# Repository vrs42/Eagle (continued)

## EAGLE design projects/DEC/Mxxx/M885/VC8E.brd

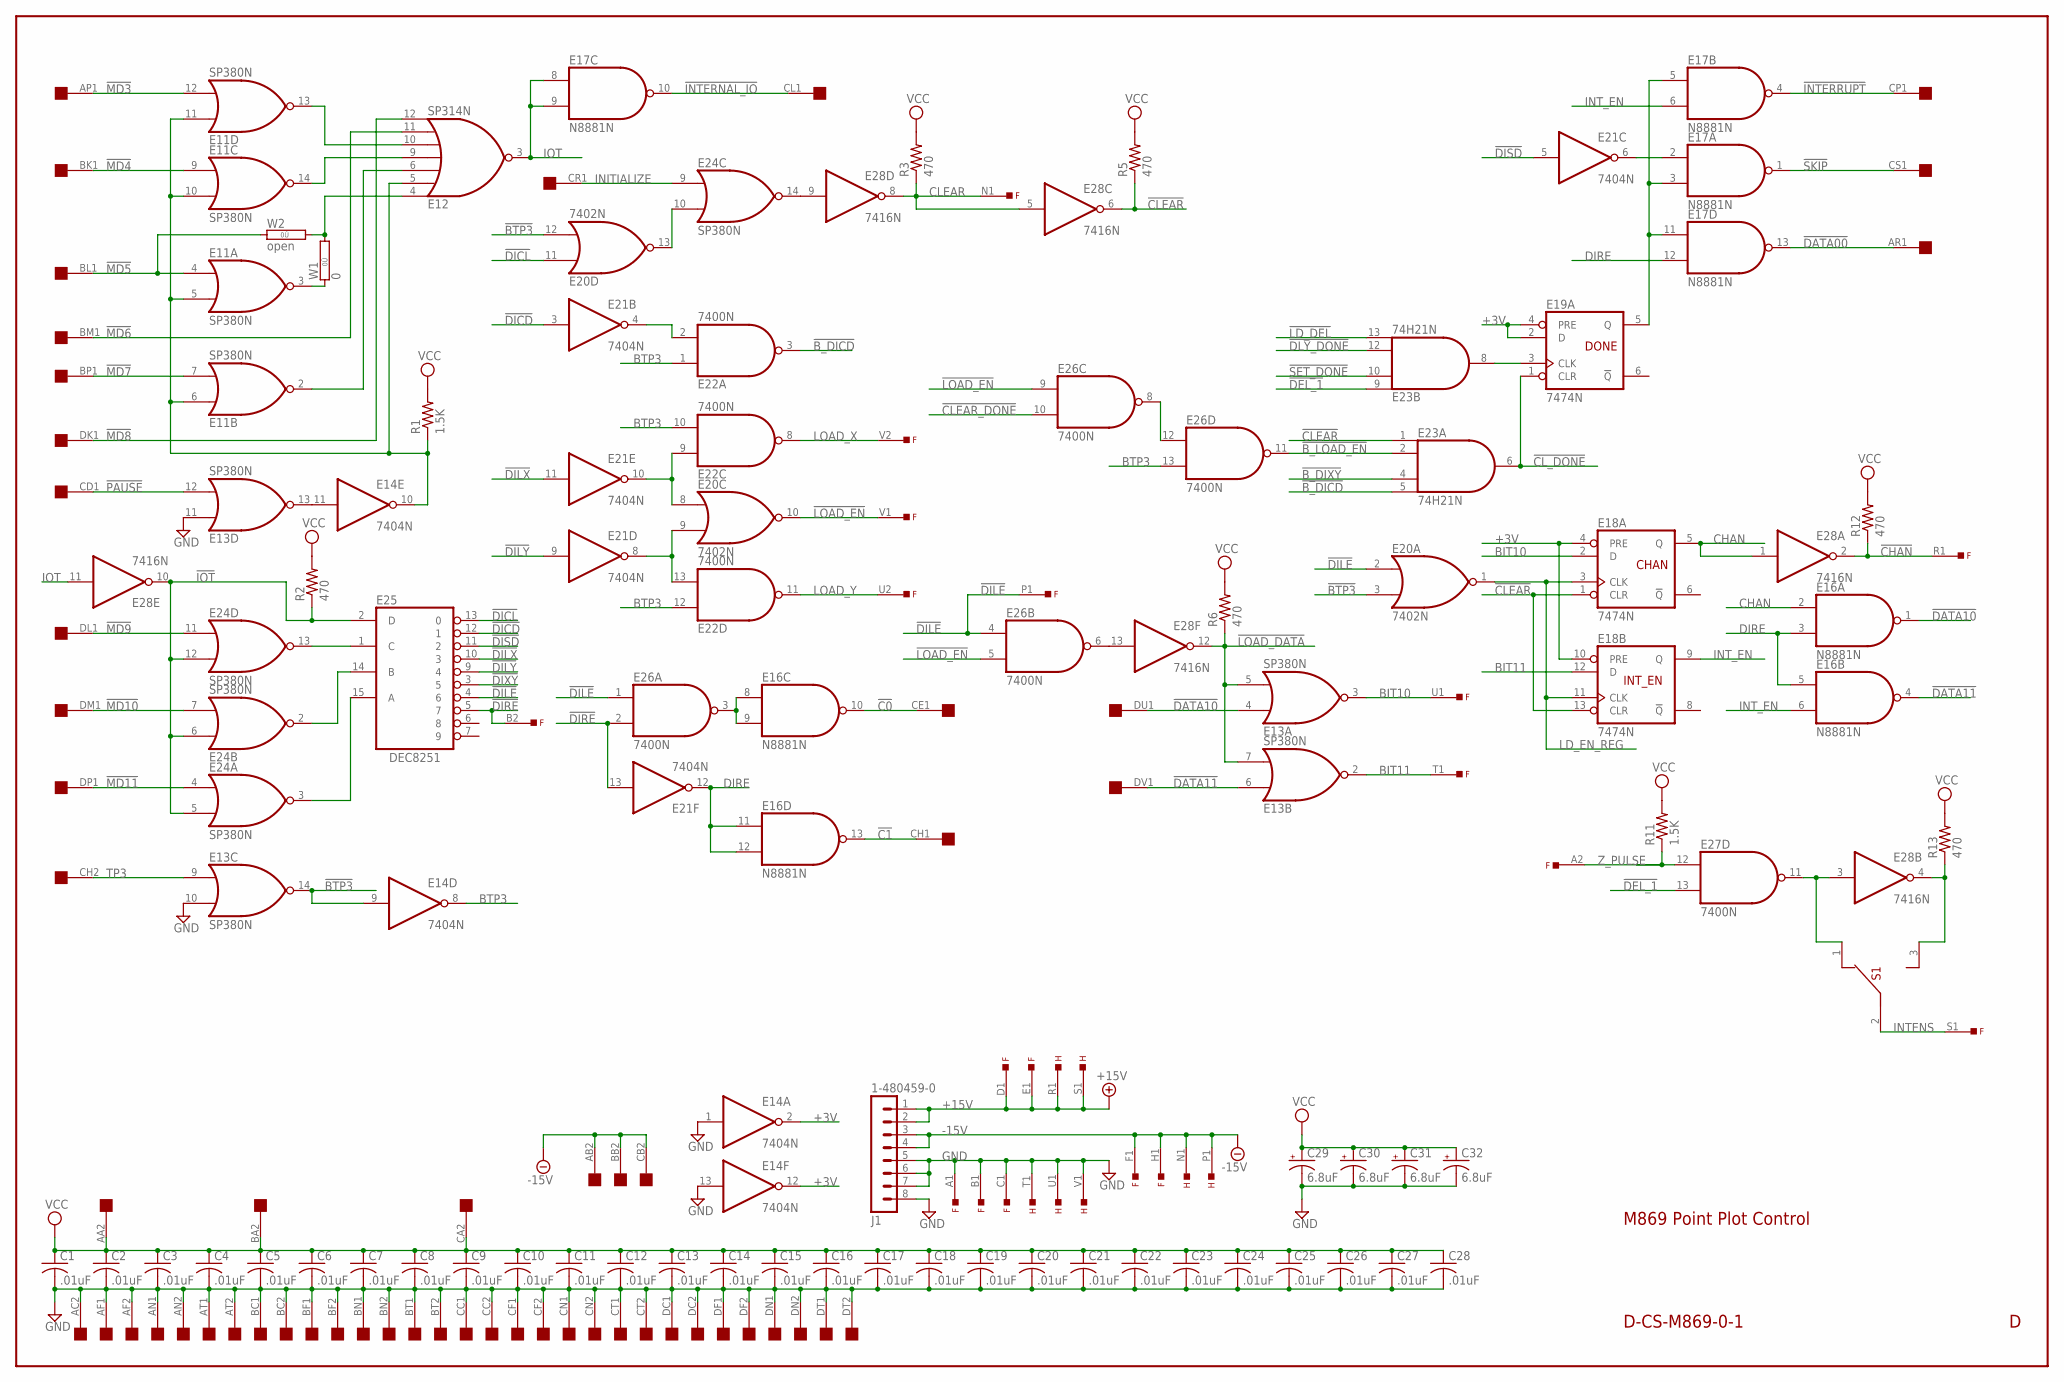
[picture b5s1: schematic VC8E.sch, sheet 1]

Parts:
C1, C2, C3, C4, C5, C6, C7, C8, C9, C10, C11, C12, C13, C14, C15, C16, C17, C18, C19, C20, C21, C22, C23, C24, C25, C26, C27, C28: .01uF; C063-025X075
C29, C30, C31, C32: 6.8uF; E12-8
E11, E13, E24: SP380N; DIL14
E12: SP314N; DIL14
E14, E21: 7404N; DIL14
E16, E17: N8881N; DIL14
E18, E19: 7474N; DIL14
E20: 7402N; DIL14
E22, E26, E27: 7400N; DIL14
E23: 74H21N; DIL14
E25: DEC8251; DIL16
E28: 7416N; DIL14
F: EDGE-TOP; EDGE-CON2
H: EDGE-TOP; EDGE-CON2
J1: 1-480459-0
OMNIBUS: QUAD; EDGE-CON8
R1, R11: 1.5K; 0207/10
R2, R3, R5, R6, R12, R13: 470; 0207/10
S1: 12-09698; 23-021
W1: 0; 0R/10
W2: open; 0R/10

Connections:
!BTP3: E13.14 (O), E14.9 (I), E20.3 (I1), E20.12 (I1)
!B_DICD: E22.3 (O), E23.5 (I3)
!B_DIXY: E23.4 (I2); also elsewhere on the board
!B_LOAD_EN: E23.2 (I1), E26.11 (O)
!C0: E16.10 (O), OMNIBUS.CE1
!C1: E16.13 (O), OMNIBUS.CH1
!CHAN: E28.2 (O), F.R1, R12.1; also elsewhere on the board
!CLEAR: E18.1 (CLR), E18.13 (CLR), E23.1 (I0), E28.6 (O), R5.1; also elsewhere on the board
!CLEAR_DONE: E26.10 (I1); also elsewhere on the board
!CL_DONE: E19.1 (CLR), E23.6 (O)
!DATA00: E17.13 (O), OMNIBUS.AR1
!DATA10: E13.4 (I0), E16.1 (O), OMNIBUS.DU1; also elsewhere on the board
!DATA11: E13.6 (I0), E16.4 (O), OMNIBUS.DV1; also elsewhere on the board
!DEL_1: E23.9 (I0), E27.13 (I1); also elsewhere on the board
!DEL_1Z: E28.4 (O), R13.1, S1.3 (A3)
!DICD: E21.3 (I), E25.12 (1)
!DICL: E20.11 (I0), E25.13 (0)
!DILE: E20.2 (I0), E25.4 (6), E26.1 (I0), E26.4 (I0), F.P1; also elsewhere on the board
!DILX: E21.11 (I), E25.10 (3)
!DILY: E21.9 (I), E25.9 (4)
!DIRE: E21.13 (I), E25.5 (7), E26.2 (I1), F.B2; also elsewhere on the board
!DISD: E21.5 (I), E25.11 (2)
!DIXY: E25.3 (5); also elsewhere on the board
!DLY_DONE: E23.12 (I2); also elsewhere on the board
!INTERNAL_IO: E17.10 (O), OMNIBUS.CL1
!INTERRUPT: E17.4 (O), OMNIBUS.CP1
!IOT: E24.5 (I1), E24.6 (I0), E24.12 (I1), E25.2 (D), E28.10 (O), R2.1
!LD_DEL: E23.13 (I3); also elsewhere on the board
!LOAD_DATA: E13.5 (I1), E13.7 (I1), E28.12 (O), R6.1; also elsewhere on the board
!LOAD_EN: E20.10 (O), E26.5 (I1), E26.9 (I0), F.V1; also elsewhere on the board
!MD3: E11.12 (I1), OMNIBUS.AP1
!MD4: E11.9 (I0), OMNIBUS.BK1
!MD5: E11.4 (I0), OMNIBUS.BL1, W2.1
!MD6: E12.11 (I5), OMNIBUS.BM1
!MD7: E11.7 (I1), OMNIBUS.BP1
!MD8: E12.12 (I6), OMNIBUS.DK1
!MD9: E24.11 (I0), OMNIBUS.DL1
!MD10: E24.7 (I1), OMNIBUS.DM1
!MD11: E24.4 (I0), OMNIBUS.DP1
!PAUSE: E13.12 (I1), OMNIBUS.CD1
!SET_DONE: E23.10 (I1); also elsewhere on the board
!SKIP: E17.1 (O), OMNIBUS.CS1
+3V: E14.2 (O), E14.12 (O), E18.4 (PRE), E18.10 (PRE), E19.2 (D), E19.4 (PRE); also elsewhere on the board
+15V: F.D1, F.E1, H.R1, H.S1, J1.1, J1.2; also elsewhere on the board
-15V: F.F1, F.H1, H.N1, H.P1, J1.3, J1.4, OMNIBUS.AB2, OMNIBUS.BB2, OMNIBUS.CB2; also elsewhere on the board
BIT10: E13.3 (O), E18.2 (D), F.U1; also elsewhere on the board
BIT11: E13.2 (O), E18.12 (D), F.T1; also elsewhere on the board
BTP3: E14.8 (O), E22.1 (I0), E22.10 (I1), E22.12 (I0), E26.13 (I1); also elsewhere on the board
CHAN: E16.2 (I0), E18.5 (Q), E28.1 (I)
CLEAR: E28.5 (I), E28.8 (O), F.N1, R3.1; also elsewhere on the board
DEL_1Z: E27.11 (O), E28.3 (I), S1.1 (A1)
DICD: E21.4 (O), E22.2 (I1)
DILX: E20.8 (I0), E21.10 (O), E22.9 (I0)
DILY: E20.9 (I1), E21.8 (O), E22.13 (I1)
DIRE: E16.3 (I1), E16.5 (I0), E16.11 (I0), E16.12 (I1), E17.12 (I1), E21.12 (O); also elsewhere on the board
DISD: E17.2 (I0), E21.6 (O)
GND: C1.2, C2.2, C3.2, C4.2, C5.2, C6.2, C7.2, C8.2, C9.2, C10.2, C11.2, C12.2, C13.2, C14.2, C15.2, C16.2, C17.2, C18.2, C19.2, C20.2, C21.2, C22.2, C23.2, C24.2, C25.2, C26.2, C27.2, C28.2, C29.-, C30.-, C31.-, C32.-, E11.1 (GND), E12.1 (GND), E13.1 (GND), E13.10 (I1), E13.11 (I0), E14.1 (I), E14.7 (GND), E14.13 (I), E16.7 (GND), E17.7 (GND), E18.7 (GND), E19.7 (GND), E20.7 (GND), E21.7 (GND), E22.7 (GND), E23.7 (GND), E24.1 (GND), E25.8 (GND), E26.7 (GND), E27.7 (GND), E28.7 (GND), F.A1, F.B1, F.C1, H.T1, H.U1, H.V1, J1.5, J1.6, J1.7, J1.8, OMNIBUS.AC2, OMNIBUS.AF1, OMNIBUS.AF2, OMNIBUS.AN1, OMNIBUS.AN2, OMNIBUS.AT1, OMNIBUS.AT2, OMNIBUS.BC1, OMNIBUS.BC2, OMNIBUS.BF1, OMNIBUS.BF2, OMNIBUS.BN1, OMNIBUS.BN2, OMNIBUS.BT1, OMNIBUS.BT2, OMNIBUS.CC1, OMNIBUS.CC2, OMNIBUS.CF1, OMNIBUS.CF2, OMNIBUS.CN1, OMNIBUS.CN2, OMNIBUS.CT1, OMNIBUS.CT2, OMNIBUS.DC1, OMNIBUS.DC2, OMNIBUS.DF1, OMNIBUS.DF2, OMNIBUS.DN1, OMNIBUS.DN2, OMNIBUS.DT1, OMNIBUS.DT2; also elsewhere on the board
INITIALIZE: E24.9 (I0), OMNIBUS.CR1
INTENS: F.S1, S1.2 (A2); also elsewhere on the board
INT_EN: E16.6 (I1), E17.6 (I1), E18.9 (Q)
IO3: E11.13 (O), E12.10 (I4)
IO4: E11.14 (O), E12.9 (I3)
IO5: E12.4 (I0), W1.2, W2.2
IO7: E11.2 (O), E12.6 (I2)
IOT: E12.3 (O), E17.8 (I0), E17.9 (I1), E28.11 (I)
LD_EN_REG: E18.3 (CLK), E18.11 (CLK), E20.1 (O); also elsewhere on the board
LOAD_X: E22.8 (O), F.V2; also elsewhere on the board
LOAD_Y: E22.11 (O), F.U2; also elsewhere on the board
MD5: E11.3 (O), W1.1
unnamed: E17.3 (I1), E17.5 (I0), E17.11 (I0), E19.5 (Q)
unnamed: E26.8 (O), E26.12 (I0)
unnamed: E19.3 (CLK), E23.8 (O)
unnamed: E16.8 (I0), E16.9 (I1), E26.3 (O)
unnamed: E26.6 (O), E28.13 (I)
unnamed: E13.13 (O), E14.11 (I)
unnamed: E24.14 (O), E28.9 (I)
unnamed: E24.3 (O), E25.15 (A)
unnamed: E24.2 (O), E25.14 (B)
unnamed: E24.13 (O), E25.1 (C)
unnamed: E20.13 (O), E24.10 (I1)
PAUSE_L: E11.5 (I1), E11.6 (I0), E11.10 (I1), E11.11 (I0), E12.5 (I1), E14.10 (O), R1.1
TP3: E13.9 (I0), OMNIBUS.CH2
VCC: C1.1, C2.1, C3.1, C4.1, C5.1, C6.1, C7.1, C8.1, C9.1, C10.1, C11.1, C12.1, C13.1, C14.1, C15.1, C16.1, C17.1, C18.1, C19.1, C20.1, C21.1, C22.1, C23.1, C24.1, C25.1, C26.1, C27.1, C28.1, C29.+, C30.+, C31.+, C32.+, E11.8 (VCC), E12.8 (VCC), E13.8 (VCC), E14.14 (VCC), E16.14 (VCC), E17.14 (VCC), E18.14 (VCC), E19.14 (VCC), E20.14 (VCC), E21.14 (VCC), E22.14 (VCC), E23.14 (VCC), E24.8 (VCC), E25.16 (VCC), E26.14 (VCC), E27.14 (VCC), E28.14 (VCC), OMNIBUS.AA2, OMNIBUS.BA2, OMNIBUS.CA2, R1.2, R2.2, R3.2, R5.2, R6.2, R11.2, R12.2, R13.2; also elsewhere on the board
Z_PULSE: E27.12 (I0), F.A2, R11.1; also elsewhere on the board

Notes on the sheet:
D-CS-M869-0-1
M869 Point Plot Control
DONE
CHAN
INT_EN

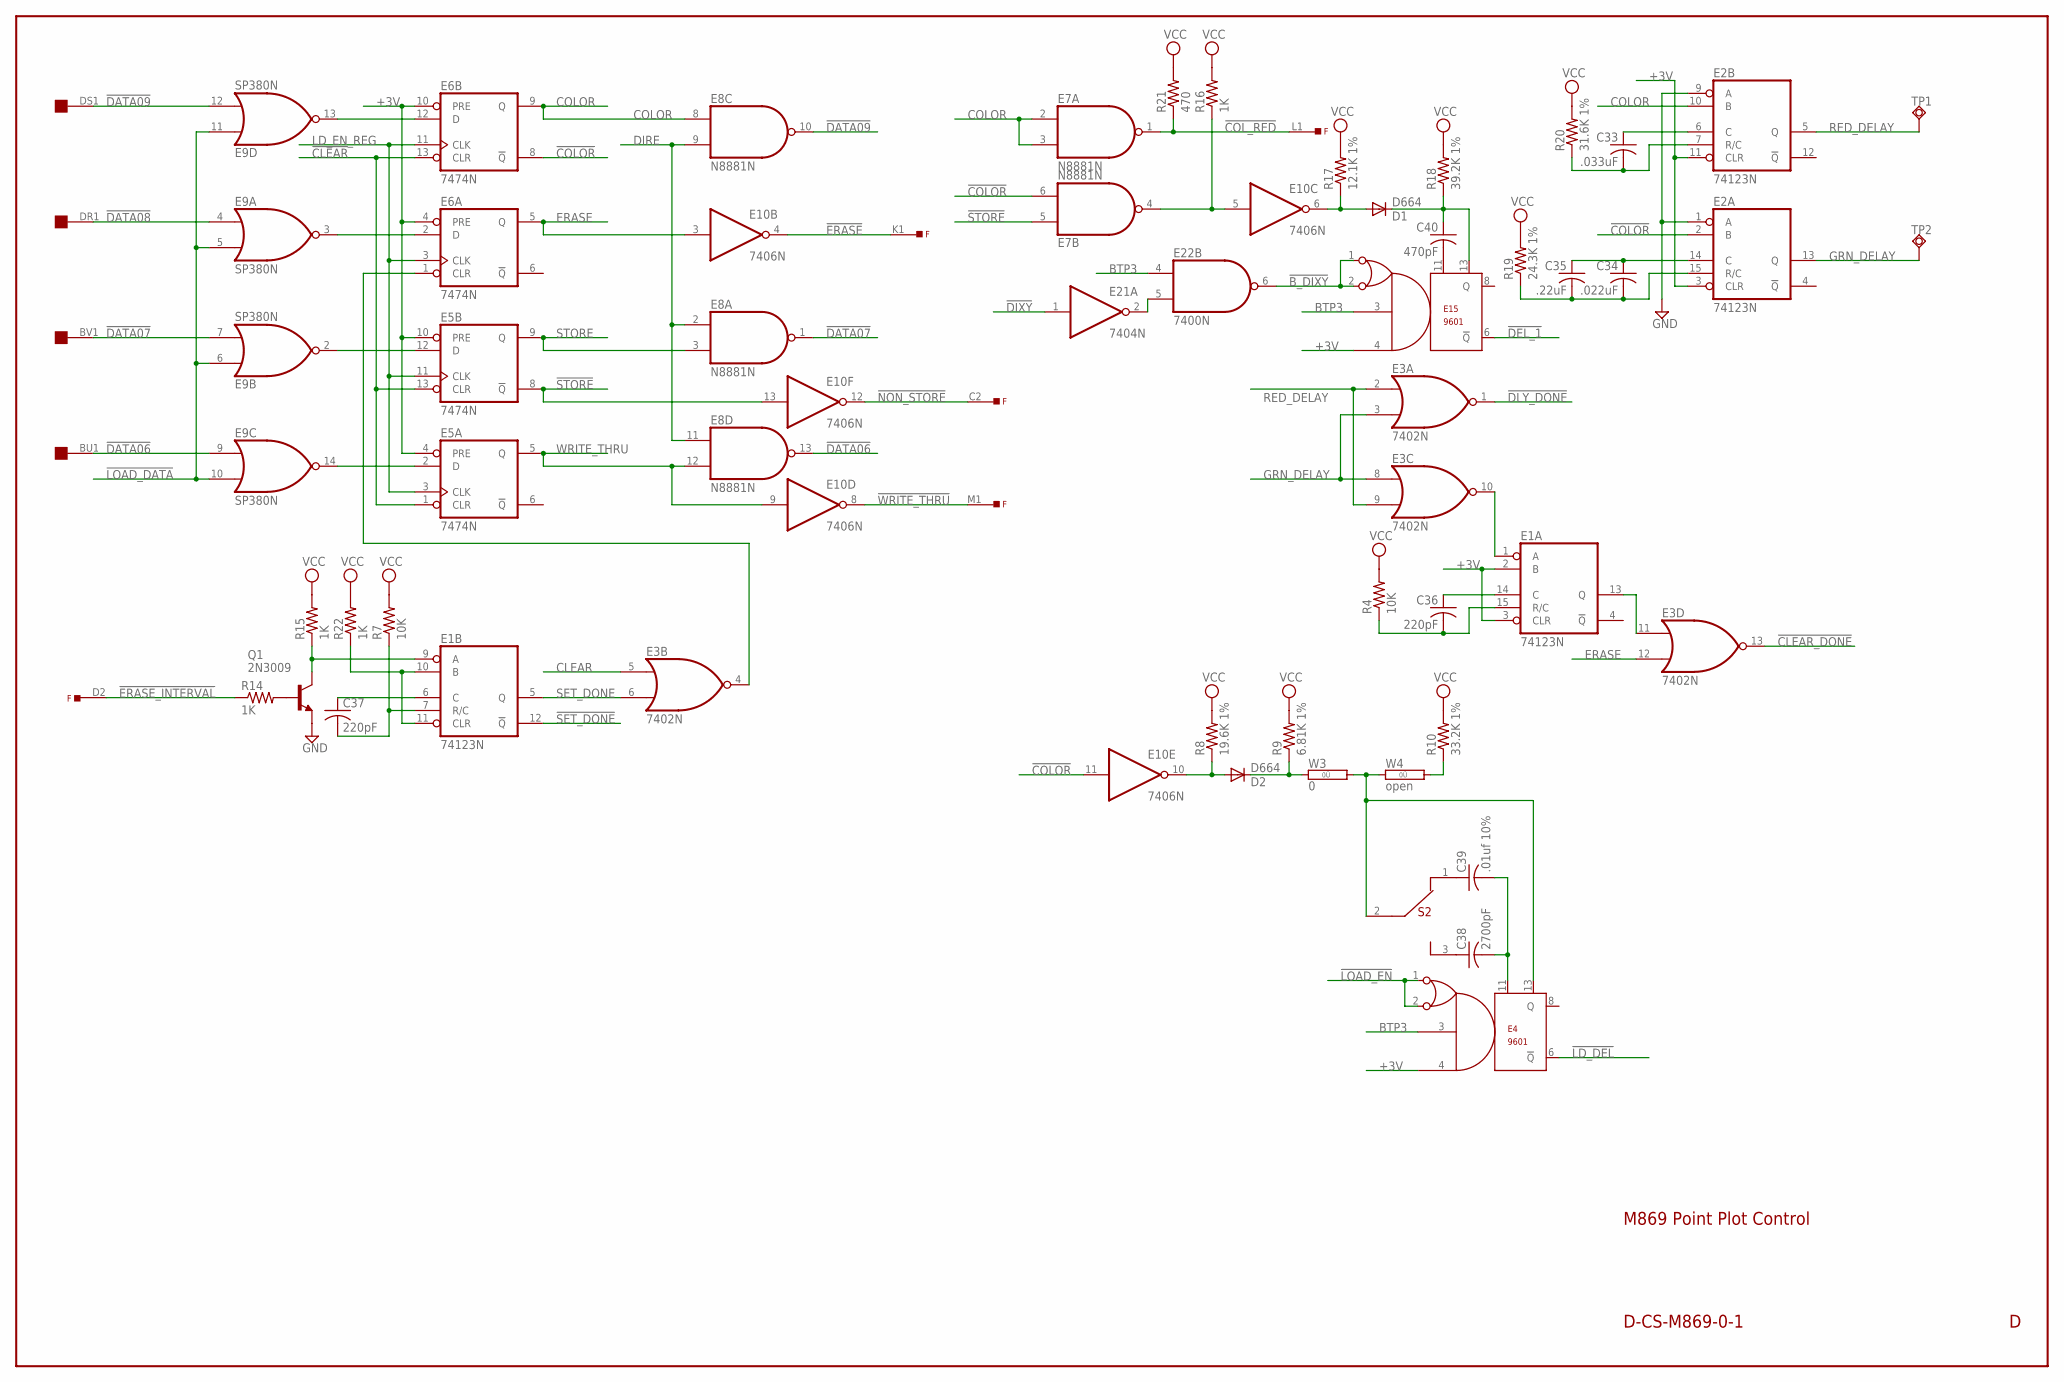
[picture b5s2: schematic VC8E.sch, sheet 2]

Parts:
C33: .033uF; C325-137X374
C34: .022uF; C203-054-229
C35: .22uF; C203-054-229
C36, C37: 220pF; C063-025X075
C38: 2700pF; C102-043X133
C39: .01uf 10%; C063-025X075
C40: 470pF; C063-025X075
D1, D2: D664; DO35-10
E1, E2: 74123N; DIL16
E3: 7402N; DIL14
E4, E15: 9601; DIL14
E5, E6: 7474N; DIL14
E7, E8: N8881N; DIL14
E9: SP380N; DIL14
E10: 7406N; DIL14
E21: 7404N; DIL14
E22: 7400N; DIL14
F: EDGE-TOP; EDGE-CON2
OMNIBUS: QUAD; EDGE-CON8
Q1: 2N3009; TO18-
R4, R7: 10K; 0207/10
R8: 19.6K 1%; 0207/15
R9: 6.81K 1%; 0207/15
R10: 33.2K 1%; 0207/15
R14, R15, R16, R22: 1K; 0207/10
R17: 12.1K 1%; 0207/15
R18: 39.2K 1%; 0207/15
R19: 24.3K 1%; 0207/15
R20: 31.6K 1%; 0207/15
R21: 470; 0207/10
S2: 12-09698; 23-021
TP1, TP2: TPSQPAD1-17; P1-17
W3: 0; 0R/10
W4: open; 0R/10

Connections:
!B_DIXY: E15.1, E15.2, E22.6 (O); also elsewhere on the board
!CLEAR: E5.1 (CLR), E5.13 (CLR), E6.13 (CLR); also elsewhere on the board
!CLEAR_DONE: E3.13 (O); also elsewhere on the board
!COLOR: E2.2 (B), E6.8 (!Q), E7.6 (I1), E10.11 (I)
!COL_RED: E7.1 (O), F.L1, R21.1; also elsewhere on the board
!DATA06: E8.13 (O), E9.9 (I0), OMNIBUS.BU1; also elsewhere on the board
!DATA07: E8.1 (O), E9.7 (I1), OMNIBUS.BV1; also elsewhere on the board
!DATA08: E9.4 (I0), OMNIBUS.DR1; also elsewhere on the board
!DATA09: E8.10 (O), E9.12 (I1), OMNIBUS.DS1; also elsewhere on the board
!DEL_1: E15.6 (!Q); also elsewhere on the board
!DIXY: E21.1 (I); also elsewhere on the board
!DLY_DONE: E3.1 (O); also elsewhere on the board
!ERASE: E10.4 (O), F.K1; also elsewhere on the board
!ERASE_INTERVAL: F.D2, R14.1; also elsewhere on the board
!LD_DEL: E4.6 (!Q); also elsewhere on the board
!LOAD_DATA: E9.5 (I1), E9.6 (I0), E9.10 (I1), E9.11 (I0); also elsewhere on the board
!LOAD_EN: E4.1, E4.2; also elsewhere on the board
!NON_STORE: E10.12 (O), F.C2; also elsewhere on the board
!SET_DONE: E1.12 (!Q); also elsewhere on the board
!STORE: E5.8 (!Q), E7.5 (I0), E10.13 (I)
!WRITE_THRU: E10.8 (O), F.M1; also elsewhere on the board
+3V: E1.2 (B), E1.3 (CLR), E2.3 (CLR), E2.11 (CLR), E4.4, E5.4 (PRE), E5.10 (PRE), E6.4 (PRE), E6.10 (PRE), E15.4; also elsewhere on the board
BCOLOR: D2.A, E10.10 (O), R8.1
BTP3: E4.3, E15.3, E22.4 (I0); also elsewhere on the board
CLEAR: E3.5 (I0); also elsewhere on the board
COLOR: E2.10 (B), E6.9 (Q), E7.2 (I0), E7.3 (I1), E8.8 (I0)
DDELAY: E1.13 (Q), E3.11 (I0)
DIRE: E8.2 (I0), E8.9 (I1), E8.11 (I0); also elsewhere on the board
DLY_DN: E1.1 (A), E3.10 (O)
ERASE: E3.12 (I1), E6.5 (Q), E10.3 (I)
GDELAY: D1.A, E10.6 (O), R17.1
GND: E1.8 (GND), E2.1 (A), E2.8 (GND), E2.9 (A), E3.7 (GND), E4.7 (GND), E5.7 (GND), E6.7 (GND), E7.7 (GND), E8.7 (GND), E9.1 (GND), E10.7 (GND), E15.7 (GND), E21.7 (GND), E22.7 (GND), Q1.1 (E); also elsewhere on the board
GRN_DELAY: E2.13 (Q), E3.3 (I1), E3.8 (I0), TP2.TP
LD_EN_REG: E5.3 (CLK), E5.11 (CLK), E6.3 (CLK), E6.11 (CLK); also elsewhere on the board
unnamed: E21.2 (O), E22.5 (I1)
unnamed: E6.12 (D), E9.13 (O)
unnamed: E5.2 (D), E9.14 (O)
unnamed: E5.12 (D), E9.2 (O)
unnamed: E6.2 (D), E9.3 (O)
unnamed: E7.4 (O), E10.5 (I), R16.1
unnamed: E3.4 (O), E6.1 (CLR)
unnamed: C40.1, D1.C, E15.13, R18.1
unnamed: C40.2, E15.11
unnamed: C34.2, C35.2, E2.15 (R/C), R19.1
unnamed: C33.2, E2.7 (R/C), R20.1
unnamed: C33.1, E2.6 (C)
unnamed: C34.1, C35.1, E2.14 (C)
unnamed: C36.2, E1.15 (R/C), R4.1
unnamed: C36.1, E1.14 (C)
unnamed: Q1.2 (B), R14.2
unnamed: E1.9 (A), Q1.3 (C), R15.1
unnamed: E1.10 (B), E1.11 (CLR), R22.1
unnamed: C37.2, E1.7 (R/C), R7.1
unnamed: C37.1, E1.6 (C)
unnamed: D2.C, R9.1, W3.1
unnamed: E4.13, S2.2 (A2), W3.2, W4.1
unnamed: R10.1, W4.2
unnamed: C39.1, S2.1 (A1)
unnamed: C38.1, S2.3 (A3)
unnamed: C38.2, C39.2, E4.11
RED_DELAY: E2.5 (Q), E3.2 (I0), E3.9 (I1), TP1.TP
SET_DONE: E1.5 (Q), E3.6 (I1)
STORE: E5.9 (Q), E8.3 (I1)
VCC: E1.16 (VCC), E2.16 (VCC), E3.14 (VCC), E4.14 (VCC), E5.14 (VCC), E6.14 (VCC), E7.14 (VCC), E8.14 (VCC), E9.8 (VCC), E10.14 (VCC), E15.14 (VCC), E21.14 (VCC), E22.14 (VCC), R4.2, R7.2, R8.2, R9.2, R10.2, R15.2, R16.2, R17.2, R18.2, R19.2, R20.2, R21.2, R22.2; also elsewhere on the board
WRITE_THRU: E5.5 (Q), E8.12 (I1), E10.9 (I)

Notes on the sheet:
D-CS-M869-0-1
M869 Point Plot Control
